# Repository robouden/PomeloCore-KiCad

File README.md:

# Pomelo Core

**Pomelo Core** is a compact radiation detection board featuring a Silicon Photomultiplier (SiPM) based sensor system with integrated high-voltage generation, analog signal processing, and USB connectivity.

## 📋 Features

- **Microcontroller**: ATSAML21G18B (ARM Cortex-M0+, 256KB Flash, 32KB RAM)
- **SiPM Interface**: Complete analog frontend with adjustable HV bias (30-70V)
- **Power Management**: Multi-rail power supply (3.3V, 3.0V, Vload, Vbias)
- **Connectivity**: USB-C interface with ESD protection
- **Debug**: 10-pin J-LINK SWD interface + 18 test points
- **Expansion**: Multiple GPIO headers for external interfaces
- **Compact**: 40mm × 100mm 4-layer PCB

## 🔧 Hardware Specifications

### Main Components

| Component | Part Number | Function |
|-----------|-------------|----------|
| MCU | ATSAML21G18B-AUT | Main microcontroller (48-pin QFN) |
| USB | USB3.1C16PFSMT | USB-C connector (USB 2.0) |
| LDO 3.3V | XC6209F332MR-G | Main 3.3V regulator |
| LDO 3.0V | TPS7A2030PDBVR | 3.0V rail for analog |
| LDO Vload | LT3014BHVES5 | Low-noise LDO for HV control |
| OpAmp | OPA357AIDBVR | Shaper amplifier |
| Comparator | TLV3201AIDBVT | Fast comparator |
| Latch | MC14043BDR2G | Digital latch for triggering |

### SiPM Sensor

- **Part Number**: AFBR-S4N44P014M (Broadcom)
- **Type**: NUV-HD Silicon Photomultiplier
- **Active Area**: 4×4 mm²
- **Spectral Range**: 350-900 nm (peak sensitivity ~420 nm)
- **Datasheet**: [AFBR-S4N44P014M Documentation](https://docs.broadcom.com/doc/AFBR-S4N44P014M-NUV-MT-Silicon-Photomultiplier)

### Scintillator Crystal

- **Material**: CsI(Tl) - Cesium Iodide doped with Thallium
- **Dimensions**: 10 mm × 10 mm × 20 mm
- **Emission Peak**: ~550 nm (matches SiPM sensitivity)
- **Application**: Gamma ray detection coupled to SiPM

### Power Supply

- **Input**: 4.5-6V via USB-C or external connector
- **Output Rails**:
  - 3.3V @ up to 200mA (digital)
  - 3.0V @ up to 100mA (analog)
  - Vload (adjustable)
  - Vbias: 30-70V @ low current (SiPM bias)

### HV Generation

The board features an integrated **boost converter + linear regulator** topology for SiPM bias generation:

- **Boost Stage**: PWM-controlled (L1 10mH inductor, Q3 P-FET, D9 Schottky)
- **Regulation**: LT3014 ultra-low-noise LDO
- **Control**: MCU DAC output (PA02_DAC_HV) sets target voltage
- **Monitoring**: Comparator feedback (PB10_HV_COMP_OUT)
- **Output**: Adjustable 30-70V Vbias for SiPM

## 📁 Project Structure

```
PomeloCore-KiCad/
├── Polemo Core/
│   └── Polemo Core 2/
│       ├── Polemo Core 2.kicad_pro       # KiCad project file
│       ├── Polemo Core 2.kicad_sch       # Schematic (organized in functional blocks)
│       ├── Polemo Core 2.kicad_pcb       # PCB layout (4-layer, 40×100mm)
│       └── Polemo Core 2-backups/        # Automatic backups
├── BOM.csv                                # Bill of Materials
├── v1_2/                                  # Version 1.2 reference files
│   └── schematic/
│       └── PomeloCore.pdf                 # V1.2 schematic PDF
└── README.md                              # This file
```

## 🎨 Schematic Organization

The schematic is organized into **7 functional blocks**:

1. **USB & POWER INPUT**: USB-C interface, power connectors, reset button
2. **POWER MANAGEMENT**: LDOs, inductors, power distribution
3. **MCU CORE**: Microcontroller, crystal, decoupling
4. **ANALOG FRONTEND**: SiPM signal chain, opamps, comparators
5. **LOGIC & CONTROL**: Digital logic, latches, level shifters
6. **EXPANSION I/O**: Pin headers for external connections
7. **DEBUG & TEST**: J-LINK interface, test points

## 🔌 Pinout & Interfaces

### J-LINK Debug Header (10-pin)
```
1: VCC        2: SWDIO
3: GND        4: SWCLK
5: GND        6: SWO
7: NC         8: NC
9: GND       10: RESET
```

### Expansion Headers

- **H2, H3**: 7-pin GPIO expansion
- **H5**: 7-pin expansion with labeled signals
- **MEAS1**: 2-pin measurement header
- **P1, P2**: 2×2 power connectors (mirrored on Pomelo Physics board)

### Key Signals

| Signal | Description |
|--------|-------------|
| SiPM_A | SiPM analog input |
| Vbias | SiPM bias voltage output |
| SHAPER_OUT | Shaped pulse output |
| PA02_DAC_HV | HV control DAC output |
| PA10_PWM | Boost converter PWM |
| PB03_PEAKDET_EN | Peak detector enable |
| PA23_TRG_OUT | Trigger output |

## 📊 Version History

### V1.3 (Current)
**Major improvements over V1.2:**

✅ **Added (47 components)**:
- USB-C connector (USBC1)
- Reset button (BUT1)
- J-LINK debug header
- 18 test points (TP1-TP18)
- Additional transistors (Q4, Q5) and diodes (D6, D8, D10)
- 15 new resistors for better signal conditioning

✅ **Changed**:
- C44: 1uF → 4.7uF
- C45: 4.7uF → 1uF
- H2, H3: 6-pin → 7-pin headers (expanded)

✅ **Enhanced**:
- Better debugging capability
- Improved power filtering
- More flexible I/O expansion

### V1.2 (Legacy)
- Initial production version
- PDF schematic available in `v1_2/schematic/`

## 🚀 Getting Started

### Prerequisites

- **KiCad 9.0** or later
- Basic understanding of radiation detection and SiPM operation
- JTAG/SWD programmer (e.g., J-Link, ST-Link)

### Opening the Project

1. Clone this repository
2. Open `Polemo Core/Polemo Core 2/Polemo Core 2.kicad_pro` in KiCad
3. The schematic shows functional blocks with dashed rectangles
4. The PCB has components organized by function

### Manufacturing

**PCB Specifications:**
- **Layers**: 4 (signal/GND/VCC/signal)
- **Dimensions**: 40mm × 100mm
- **Thickness**: 1.6mm
- **Copper**: 35μm (1oz) on all layers
- **Min Track/Space**: 0.15mm / 0.15mm (for 0805 components)
- **Finish**: HASL or ENIG recommended
- **Solder Mask**: Green (top and bottom)

**Assembly Notes:**
- Minimum component size: 0805 for passives
- QFN-48 MCU requires reflow soldering
- LDOs are SOT-23-5 packages
- Test points for easy debugging

## 📝 Design Notes

### Power Planes
- **Layer 1 (In1.Cu)**: GND plane - solid pour for low noise
- **Layer 2 (In2.Cu)**: VCC plane - split for 3.3V/3.0V rails

### Critical Traces
- Keep SiPM analog traces short and shielded
- HV traces (Vbias) should be isolated from digital signals
- Crystal traces should be short with GND guard ring

### Component Placement
Components are organized into functional blocks:
- Power supply on left side
- MCU in center
- Analog section on right
- Digital logic bottom-right

## 🔬 Applications

- Radiation detection and measurement
- Scintillation counting
- Environmental monitoring
- Educational radiation physics
- DIY Geiger counter replacement with better sensitivity

## 👥 Credits

**Designer**: M. Cuciuc
**Organization**: Safecast
**Date**: 2024-2025

## 📄 License

This hardware design is open source. Please check individual files for specific license terms.

Firmware and software components may have separate licenses.

## 🤝 Contributing

Contributions are welcome! Please:

1. Fork the repository
2. Create a feature branch
3. Make your changes
4. Submit a pull request

For major changes, please open an issue first to discuss what you would like to change.

## 📞 Support

- **Project Page**: [Pomelo on Crowd Supply](https://www.crowdsupply.com/pomelo-instrumentation/pomelo)
- **Safecast**: [https://safecast.org](https://safecast.org)
- Report issues through the repository's issue tracker

## ⚠️ Safety Warning

This board generates **high voltage** (up to 70V) for SiPM biasing. Handle with care:
- Do not touch HV traces while powered
- Use proper ESD protection
- Follow safe electronics handling practices
- Designed for educational and research purposes

---

**Made with ❤️ for the radiation detection community**

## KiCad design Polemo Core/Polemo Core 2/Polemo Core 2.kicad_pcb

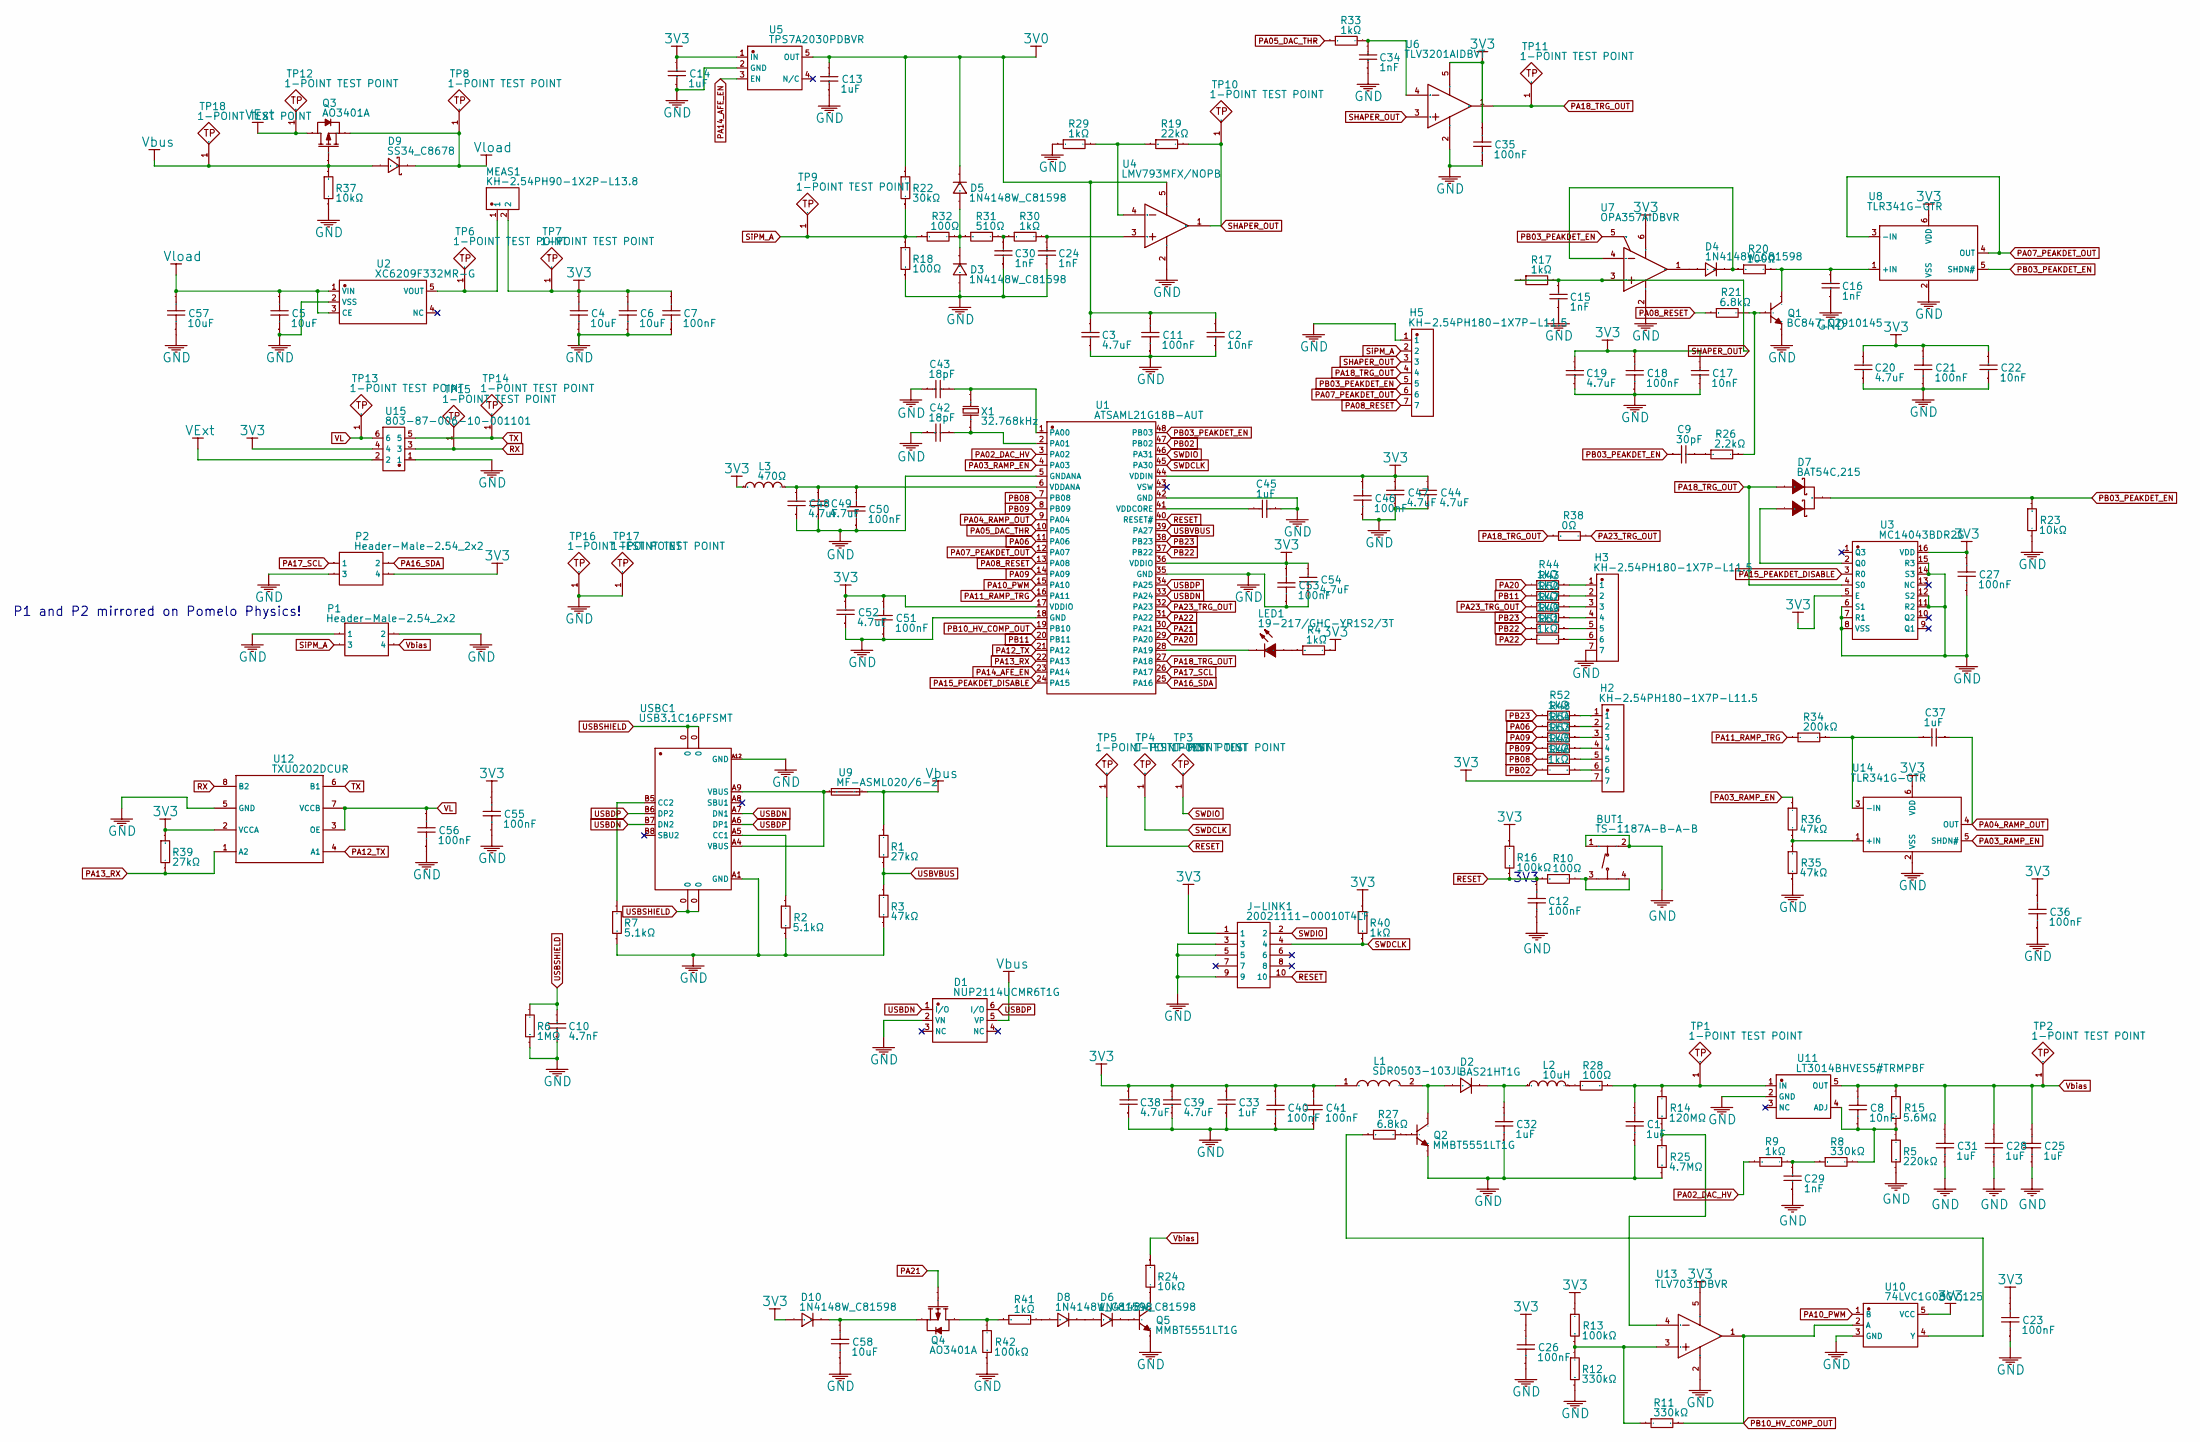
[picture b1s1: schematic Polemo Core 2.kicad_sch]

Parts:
BUT1: TS-1187A-B-A-B; SW_SPST_TL3342; Manufacturer Part TS-1187A-B-A-B
C1, C32: 1uF; C_0805_2012Metric; Manufacturer Part GRM55DR72D105KW01L
C2, C17, C22: 10nF; C_0805_2012Metric; Manufacturer Part 0603B103K500NT
C3, C19, C20: 4.7uF; C_0805_2012Metric; Manufacturer Part 1206B475K500NT
C4, C5, C6, C57, C58: 10uF; C_1206_3216Metric; Manufacturer Part CL10A106KP8NNNC
C7, C11, C12, C18, C21, C23, C26, C27, C35, C36, C40, C41, C46, C50, C51, C53, C55, C56: 100nF; C_0805_2012Metric; Manufacturer Part CC0603KRX7R9BB104
C8: 10nF; C_0805_2012Metric; Manufacturer Part 12062C103KAT2A
C9: 30pF; C_0805_2012Metric; Manufacturer Part 0603CG300J500NT
C10: 4.7nF; C_0805_2012Metric; Manufacturer Part 0603B472K500NT
C13, C14, C33, C37, C45: 1uF; C_0805_2012Metric; Manufacturer Part CL10A105KB8NNNC
C15, C16, C24, C29, C30, C34: 1nF; C_0805_2012Metric; Manufacturer Part CL10B102KB8NNNC
C25, C28, C31: 1uF; C_0805_2012Metric; Manufacturer Part 08051C105KAT2A
C38, C39: 4.7uF; C_1812_4532Metric; Manufacturer Part 1206B475K500NT
C42, C43: 18pF; C_0805_2012Metric; Manufacturer Part CL10C180JB8NNNC
C44, C47, C48, C49, C52, C54: 4.7uF; C_0805_2012Metric; Manufacturer Part CL10A475KO8NNNC
D1: NUP2114UCMR6T1G; SO-8_3.9x4.9mm_P1.27mm; Manufacturer Part NUP2114UCMR6T1G
D2: BAS21HT1G; SOT-23; Manufacturer Part BAS21HT1G
D3, D4, D5, D6, D8, D10: 1N4148W_C81598; D_SOD-123; Manufacturer Part 1N4148W
D7: BAT54C,215; SOT-23; Manufacturer Part BAT54C,215
D9: SS34_C8678; D_SMA; Manufacturer Part SS34
H2, H3, H5: KH-2.54PH180-1X7P-L11.5; PinHeader_1x07_P2.54mm_Vertical; Manufacturer Part KH-2.54PH180-1X7P-L11.5
J-LINK1: 20021111-00010T4LF; PinHeader_2x05_P2.54mm_Vertical; Manufacturer Part 20021111-00010T4LF
L1: SDR0503-103JL; L_0805_2012Metric
L2: 10uH; L_1210_3225Metric; Manufacturer Part SDFL1608S100KTF
L3: 470Ω; L_1210_3225Metric; Manufacturer Part BLM18PG471SN1D
LED1: 19-217/GHC-YR1S2/3T; LED_0805_2012Metric; Manufacturer Part 19-217/GHC-YR1S2/3T
MEAS1: KH-2.54PH90-1X2P-L13.8; PinHeader_1x02_P2.54mm_Vertical; Manufacturer Part KH-2.54PH90-1X2P-L13.8
P1, P2: Header-Male-2.54_2x2; PinHeader_2x02_P2.54mm_Vertical; Manufacturer Part 2.54-2*2P针
Q1: BC847_C2910145; SOT-23; Manufacturer Part BC847
Q2, Q5: MMBT5551LT1G; SOT-23; Manufacturer Part MMBT5551LT1G
Q3, Q4: AO3401A; SOT-23; Manufacturer Part AO3401A
R1, R39: 27kΩ; R_0805_2012Metric; Manufacturer Part 0603WAF2702T5E
R2, R7: 5.1kΩ; R_0805_2012Metric; Manufacturer Part 0603WAF5101T5E
R3, R35, R36: 47kΩ; R_0805_2012Metric; Manufacturer Part 0603WAF4702T5E
R4, R9, R17, R29, R30, R33, R40, R41, R43, R44, R45, R46, R47, R48, R49, R50, R51, R52, R53, R54: 1kΩ; R_0805_2012Metric; Manufacturer Part 0603WAF1001T5E
R5: 220kΩ; R_0805_2012Metric; Manufacturer Part 0603WAF2203T5E
R6: 1MΩ; R_0805_2012Metric; Manufacturer Part 0603WAF1004T5E
R8, R11, R12: 330kΩ; R_0805_2012Metric; Manufacturer Part 0603WAF3303T5E
R10, R18, R20, R28, R32: 100Ω; R_0805_2012Metric; Manufacturer Part 0603WAF1000T5E
R13, R16, R42: 100kΩ; R_0805_2012Metric; Manufacturer Part 0603WAF1003T5E
R14: 120MΩ; R_0805_2012Metric; Manufacturer Part 0603WAF4704T5E
R15: 5.6MΩ; R_0805_2012Metric; Manufacturer Part 0603WAF5604T5E
R19: 22kΩ; R_0805_2012Metric; Manufacturer Part 0603WAF2202T5E
R21, R27: 6.8kΩ; R_0805_2012Metric; Manufacturer Part 0603WAF6801T5E
R22: 30kΩ; R_0805_2012Metric; Manufacturer Part 0603WAF3002T5E
R23, R24, R37: 10kΩ; R_0805_2012Metric; Manufacturer Part 0603WAF1002T5E
R25: 4.7MΩ; R_0805_2012Metric; Manufacturer Part 0603WAF4704T5E
R26: 2.2kΩ; R_0805_2012Metric; Manufacturer Part 0603WAF2201T5E
R31: 510Ω; R_0805_2012Metric; Manufacturer Part 0603WAF5100T5E
R34: 200kΩ; R_0805_2012Metric; Manufacturer Part 0603WAF2003T5E
R38: 0Ω; R_0805_2012Metric; Manufacturer Part 0603WAF0000T5E
TP1, TP2, TP3, TP4, TP5, TP6, TP7, TP8, TP9, TP10, TP11, TP12, TP13, TP14, TP15, TP16, TP17, TP18: 1-POINT TEST POINT; TestPoint_Pad_D1.5mm
U1: ATSAML21G18B-AUT; QFN-48-1EP_7x7mm_P0.5mm_EP5.15x5.15mm; Manufacturer Part ATSAML21G18B-AUT
U2: XC6209F332MR-G; SOT-23-5; Manufacturer Part XC6209F332MR-G
U3: MC14043BDR2G; SOIC-16_3.9x9.9mm_P1.27mm; Manufacturer Part MC14043BDR2G
U4: LMV793MFX/NOPB; MSOP-8_3x3mm_P0.65mm; Manufacturer Part LMV793MFX/NOPB
U5: TPS7A2030PDBVR; SOT-23-5; Manufacturer Part TPS7A2030PDBVR
U6: TLV3201AIDBVT; SOT-23-5; Manufacturer Part TLV3201AIDBVT
U7: OPA357AIDBVR; SOT-23-5; Manufacturer Part OPA357AIDBVR
U8, U14: TLR341G-GTR; SOT-23-6; Manufacturer Part TLR341G-GTR
U9: MF-ASML020/6-2; SOIC-8_3.9x4.9mm_P1.27mm; Manufacturer Part MF-ASML020/6-2
U10: 74LVC1G08GV,125; SOT-353_SC-70-5; Manufacturer Part 74LVC1G08GV,125
U11: LT3014BHVES5#TRMPBF; SOT-23-5; Manufacturer Part LT3014BHVES5#TRMPBF
U12: TXU0202DCUR; VSSOP-8_2.3x2mm_P0.5mm; Manufacturer Part TXB0102DCUR
U13: TLV7031DBVR; SOT-23-5; Manufacturer Part TLV7031DBVR
U15: 803-87-006-10-001101; PinSocket_1x06_P2.54mm_Vertical; Manufacturer Part 803-87-006-10-001101
USBC1: USB3.1C16PFSMT; USB_C_Receptacle_HRO_TYPE-C-31-M-12
X1: 32.768kHz; Crystal_SMD_3225-4Pin_3.2x2.5mm; Manufacturer Part Q13FC1350000400

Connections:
3V0: C2.2, C3.2, C11.2, C13.2, D5.1 (K), R22.2, U4.5 (V+), U5.5 (OUT)
3V3: C4.2, C6.2, C7.2, C14.2, C17.2, C18.2, C19.2, C20.2, C21.2, C22.2, C23.2, C26.2, C27.2, C33.2, C35.2, C36.2, C38.2, C39.2, C40.2, C41.2, C44.2, C46.2, C47.2, C51.2, C52.2, C53.2, C54.2, C55.2, D10.2 (A), H2.7, J-LINK1.1, L1.1, L3.1, MEAS1.2, P2.4, R4.2, R13.2, R16.2, R39.1, R40.2, TP7.1, U1.17 (VDDIO), U1.36 (VDDIO), U1.44 (VDDIN), U3.5 (E), U3.16 (VDD), U5.1 (IN), U6.5 (VCC), U7.6 (V+), U8.6 (VDD), U10.5 (VCC), U12.2 (VCCA), U13.5 (VCC), U14.6 (VDD), U15.4
GND: BUT1.1 (A), BUT1.2 (B), C1.1, C2.1, C3.1, C4.1, C5.1, C6.1, C7.1, C10.1, C11.1, C12.2, C13.1, C14.1, C15.1, C16.1, C17.1, C18.1, C19.1, C20.1, C21.1, C22.1, C23.1, C24.1, C25.1, C26.1, C27.1, C28.1, C29.1, C30.1, C31.1, C32.1, C33.1, C34.1, C35.1, C36.1, C38.1, C39.1, C40.1, C41.1, C42.1, C43.1, C44.1, C45.1, C46.1, C47.1, C48.1, C49.1, C50.1, C51.1, C52.1, C53.1, C54.1, C55.1, C56.1, C57.1, C58.1, D1.2 (VN), D3.2 (A), H3.7, H5.1, J-LINK1.3, J-LINK1.5, J-LINK1.9, P1.1, P1.2, P2.3, Q1.2 (E), Q2.2 (E), Q5.2 (E), R2.1, R3.1, R5.1, R6.1, R7.1, R12.1, R18.1, R23.2, R25.1, R29.1, R35.1, R37.2, R42.1, TP16.1, TP17.1, U1.5 (GNDANA), U1.18 (GND), U1.35 (GND), U1.42 (GND), U2.2 (VSS), U3.6 (S1), U3.7 (R1), U3.8 (VSS), U3.11 (R2), U3.12 (S2), U3.14 (S3), U3.15 (R3), U4.2 (V-), U5.2 (GND), U6.2 (GND), U7.2 (V-), U8.2 (VSS), U10.3 (GND), U11.2 (GND), U12.5 (GND), U13.2 (VEE), U14.2 (VSS), U15.1, USBC1.A1 (GND), USBC1.A12 (GND)
unnamed: BUT1.3 (C), BUT1.4 (D), R10.2
unnamed: C9.2, R26.1
unnamed: C29.2, R8.1, R9.2
unnamed: C30.2, R30.1, R31.2
unnamed: D2.2 (A), L1.2, Q2.3 (C)
unnamed: C32.2, D2.1 (C), L2.1
unnamed: D3.1 (K), D5.2 (A), R31.1, R32.2
unnamed: D4.2 (A), U7.1 (OUT)
unnamed: D4.1 (K), R20.1, U7.4 (IN-)
unnamed: D6.2 (A), D8.1 (K)
unnamed: D6.1 (K), Q5.1 (B)
unnamed: D8.2 (A), R41.2
unnamed: C58.2, D10.1 (K), Q4.2 (S)
unnamed: H2.1, R52.1
unnamed: H2.2, R48.1
unnamed: H2.3, R54.1
unnamed: H2.4, R53.1
unnamed: H2.5, R45.1
unnamed: H2.6, R46.1
unnamed: H3.1, R44.1
unnamed: H3.2, R43.1
unnamed: H3.3, R50.1
unnamed: H3.4, R47.1
unnamed: H3.5, R49.1
unnamed: H3.6, R51.1
unnamed: L2.2, R28.2
unnamed: LED1.2 (A), R4.1
unnamed: LED1.1 (C), U1.28 (PA19)
unnamed: Q1.1 (B), R21.2, R26.2
unnamed: C16.2, Q1.3 (C), R20.2, U8.1 (+IN)
unnamed: Q2.1 (B), R27.2
unnamed: Q4.3 (D), R41.1, R42.2
unnamed: Q5.3 (C), R24.2
unnamed: C43.2, U1.1 (PA00), X1.2
unnamed: C42.2, U1.2 (PA01), X1.1
unnamed: C48.2, C49.2, C50.2, L3.2, U1.6 (VDDANA)
unnamed: C45.2, U1.41 (VDDCORE)
unnamed: MEAS1.1, TP6.1, U2.5 (VOUT)
unnamed: D7.2 (A), U3.2 (Q0)
unnamed: C24.2, R30.2, U4.3 (+IN)
unnamed: R19.1, R29.2, U4.4 (-IN)
unnamed: C34.2, R33.2, U6.4 (VIN-)
unnamed: U9.1, USBC1.A4 (VBUS), USBC1.A9 (VBUS)
unnamed: R27.1, U10.4 (Y)
unnamed: C8.1, R5.2, R8.2, R15.1, U11.4 (ADJ)
unnamed: C1.2, R14.2, R28.1, TP1.1, U11.1 (IN)
unnamed: R11.2, R12.2, R13.1, U13.3 (IN+)
unnamed: R14.1, R25.2, U13.4 (IN-)
unnamed: R35.2, R36.1, U14.1 (+IN)
unnamed: C37.2, R34.2, U14.3 (-IN)
unnamed: R2.2, USBC1.A5 (CC1)
unnamed: R7.2, USBC1.B5 (CC2)
PA02_DAC_HV: R9.1, U1.3 (PA02)
PA03_RAMP_EN: R36.2, U1.4 (PA03), U14.5 (SHDN#)
PA04_RAMP_OUT: C37.1, U1.9 (PA04), U14.4 (OUT)
PA05_DAC_THR: R33.1, U1.10 (PA05)
PA06: R48.2, U1.11 (PA06)
PA07_PEAKDET_OUT: H5.6, U1.12 (PA07), U8.3 (-IN), U8.4 (OUT)
PA08_RESET: H5.7, R21.1, U1.13 (PA08)
PA09: R54.2, U1.14 (PA09)
PA10_PWM: U1.15 (PA10), U10.1 (B)
PA11_RAMP_TRG: R34.1, U1.16 (PA11)
PA12_TX: U1.21 (PA12), U12.4 (A1)
PA13_RX: R39.2, U1.22 (PA13), U12.1 (A2)
PA14_AFE_EN: U1.23 (PA14), U5.3 (EN)
PA15_PEAKDET_DISABLE: U1.24 (PA15), U3.3 (R0)
PA16_SDA: P2.2, U1.25 (PA16)
PA17_SCL: P2.1, U1.26 (PA17)
PA18_TRG_OUT: D7.1 (A), H5.4, R38.1, TP11.1, U1.27 (PA18), U3.4 (S0), U6.1 (OUT)
PA20: R44.2, U1.29 (PA20)
PA21: Q4.1 (G), U1.30 (PA21)
PA22: R51.2, U1.31 (PA22)
PA23_TRG_OUT: R38.2, R50.2, U1.32 (PA23)
PB02: R46.2, U1.47 (PB02)
PB03_PEAKDET_EN: C9.1, D7.3 (K), H5.5, R23.1, U1.48 (PB03), U7.5 (ENABLE), U8.5 (SHDN#)
PB08: R45.2, U1.7 (PB08)
PB09: R53.2, U1.8 (PB09)
PB10_HV_COMP_OUT: R11.1, U1.19 (PB10), U10.2 (A), U13.1 (OUT)
PB11: R43.2, U1.20 (PB11)
PB22: R49.2, U1.37 (PB22)
PB23: R47.2, R52.2, U1.38 (PB23)
RESET: C12.1, J-LINK1.10, R10.1, R16.1, TP5.1, U1.40 (RESET#)
RX: TP15.1, U12.8 (B2), U15.3
SHAPER_OUT: C15.2, H5.3, R17.1, R17.2, R19.2, TP10.1, U4.1 (OUTPUT), U6.3 (VIN+), U7.3 (IN+)
SWDCLK: J-LINK1.4, R40.1, TP4.1, U1.45 (PA30)
SWDIO: J-LINK1.2, TP3.1, U1.46 (PA31)
SiPM_A: H5.2, P1.3, R18.2, R22.1, R32.1, TP9.1
TX: TP14.1, U12.6 (B1), U15.5
USBDN: D1.1 (I/O), U1.33 (PA24), USBC1.A7 (DN1), USBC1.B7 (DN2)
USBDP: D1.6 (I/O), U1.34 (PA25), USBC1.A6 (DP1), USBC1.B6 (DP2)
USBSHIELD: C10.2, R6.2, USBC1.0
USBVBUS: R1.1, R3.2, U1.39 (PA27)
VExt: Q3.3 (D), TP12.1, U15.2
VL: C56.2, TP13.1, U12.3 (OE), U12.7 (VCCB), U15.6
Vbias: C8.2, C25.2, C28.2, C31.2, P1.4, R15.2, R24.1, TP2.1, U11.5 (OUT)
Vbus: D1.5 (VP), D9.2 (A), Q3.1 (G), R1.2, R37.1, TP18.1, U9.2
Vload: C5.2, C57.2, D9.1 (K), Q3.2 (S), TP8.1, U2.1 (VIN), U2.3 (CE)

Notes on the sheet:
3V3
P1 and P2 mirrored on Pomelo Physics!

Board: 4 copper layers, 174 parts (0 on the bottom side), 99 nets, no tracks yet.

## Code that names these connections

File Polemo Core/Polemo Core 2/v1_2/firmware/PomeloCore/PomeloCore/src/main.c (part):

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static void isr_vbus_callback(void)
{
	volatile uint8_t a;
	a = port_pin_get_input_level(PIN_PA09);
	isr_vbus = true;
}

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	static uint16_t adc_val, rnd, i;
	static volatile bool pinValue;
	static uint32_t l_gammaTime;
	pinValue = port_pin_get_input_level(PIN_PB02);

	if (daq_enabled)
	{
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		while (adc_read(&adc_instance_app, &adc_val) == STATUS_BUSY) ;

		// Clear peak detector capacitor
		port_pin_set_output_level(PIN_PA08, 1);
		port_pin_set_output_level(PIN_PA15, 1);
		nop(); nop(); nop(); nop(); nop(); // 5us. Aaaactually almost nothing
		port_pin_set_output_level(PIN_PA15, 0);
		port_pin_set_output_level(PIN_PA08, 0);


		if (gammaDaqRun)
		{
			port_pin_set_output_level(PIN_PA19, 0);
			
			adc_val >>= 2;
			
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
			if (gammaCoincidence)
			{
				if (port_pin_get_input_level(PIN_PA20))
				{
					gammaSpectrumCoincidence[adc_val]++;
					gammaPulseCoincidenceN++;
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					}
					
					// Assert our ACK line
					port_pin_set_output_level(PIN_PB11, 1);
					// Loop while monitor line is still high
					while (port_pin_get_input_level(PIN_PA20)) ;
					// Deassert our ACK line
					port_pin_set_output_level(PIN_PB11, 0);
				}
			}
			else
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			
		}

		port_pin_set_output_level(PIN_PA19, 1);
		
		// Try to fix subthreshold structures. Retriggering of this interrupt can
		// cause a 2nd reading, after the peak detector had already been cleared
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	struct ccl_lut_config ccl_lut_conf;
	struct system_pinmux_config pinmux_config;

	// Set PA22 as remote trigger input - CCL2 In0
	system_pinmux_get_config_defaults(&pinmux_config);
	pinmux_config.mux_position = 8;
	pinmux_config.direction    = SYSTEM_PINMUX_PIN_DIR_INPUT;
	pinmux_config.input_pull   = SYSTEM_PINMUX_PIN_PULL_DOWN;
	system_pinmux_pin_set_config(PIN_PA22, &pinmux_config);

	// Set PA23 as local trigger input - CCL2 In1
	system_pinmux_get_config_defaults(&pinmux_config);
	pinmux_config.mux_position = 8;
	pinmux_config.direction    = SYSTEM_PINMUX_PIN_DIR_INPUT;
	pinmux_config.input_pull   = SYSTEM_PINMUX_PIN_PULL_DOWN;
	system_pinmux_pin_set_config(PIN_PA23, &pinmux_config);

	// Set PB22 as ACK0 input - CCL0 In0
	system_pinmux_get_config_defaults(&pinmux_config);
	pinmux_config.mux_position = 8;
	pinmux_config.direction    = SYSTEM_PINMUX_PIN_DIR_INPUT;
	pinmux_config.input_pull   = SYSTEM_PINMUX_PIN_PULL_DOWN;
	system_pinmux_pin_set_config(PIN_PB22, &pinmux_config);

	// Set PA06 as ACK1 input - CCL0 In2
	system_pinmux_get_config_defaults(&pinmux_config);
	pinmux_config.mux_position = 8;
	pinmux_config.direction    = SYSTEM_PINMUX_PIN_DIR_INPUT;
	pinmux_config.input_pull   = SYSTEM_PINMUX_PIN_PULL_DOWN;
	system_pinmux_pin_set_config(PIN_PA06, &pinmux_config);

	// Set PB23 as coincidences output - CCL0 out
	system_pinmux_get_config_defaults(&pinmux_config);
	pinmux_config.mux_position = 8;
	pinmux_config.direction    = SYSTEM_PINMUX_PIN_DIR_OUTPUT_WITH_READBACK;
	system_pinmux_pin_set_config(PIN_PB23, &pinmux_config);

	ccl_module_reset();

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	system_pinmux_get_config_defaults(&pinmux_config);
	pinmux_config.mux_position = 7;
	pinmux_config.direction    = PORT_PIN_DIR_OUTPUT;
	system_pinmux_pin_set_config(PIN_PA10, &pinmux_config);
}

void hv_disable(void)
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
	// HV PWM output 0
	pin_conf.direction  = PORT_PIN_DIR_OUTPUT;
	port_pin_set_config(PIN_PA10, &pin_conf);
	port_pin_set_output_level(PIN_PA10, 0);
	
	// Pulse HV crowbar
	port_pin_set_output_level(PIN_PA21, 0);
	delay_ms(10);
	port_pin_set_output_level(PIN_PA21, 1);
}

void hv_boost(bool boostOn)
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	pinmux_config.direction    = SYSTEM_PINMUX_PIN_DIR_INPUT;
	pinmux_config.input_pull   = SYSTEM_PINMUX_PIN_PULL_NONE;
	pinmux_config.powersave    = false;
	system_pinmux_pin_set_config(PIN_PA18, &pinmux_config);

	spi_transceive_wait(&spi_instance_app, 0xFF, &rx_data);
	spi_transceive_wait(&spi_instance_app, 0xFF, &rx_data);
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	uint16_t rx_data_1;
	
	// One-shot conversion request
	port_pin_set_output_level(PIN_PA27, 0);
	spi_transceive_wait(&spi_instance_app, 0x00, &rx_data_0);
	spi_transceive_wait(&spi_instance_app, 0x06, &rx_data_0);
	spi_transceive_wait(&spi_instance_app, 0x16, &rx_data_0);	// One shot mode, 1 Hz conversion rate
	spi_transceive_wait(&spi_instance_app, 0x00, &rx_data_1);
	port_pin_set_output_level(PIN_PA27, 1);

	delay_ms(15);

	// Read result
	port_pin_set_output_level(PIN_PA27, 0);
	spi_transceive_wait(&spi_instance_app, 0x01, &rx_data_0);
	spi_transceive_wait(&spi_instance_app, 0x00, &rx_data_0);
	spi_transceive_wait(&spi_instance_app, 0x00, &rx_data_0);
	spi_transceive_wait(&spi_instance_app, 0x00, &rx_data_0);
	spi_transceive_wait(&spi_instance_app, 0x00, &rx_data_1);
	port_pin_set_output_level(PIN_PA27, 1);

	rx_data_0 |= rx_data_1 << 8;
	rx_data_0 >>= 2;
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	
	// Ramp generator enable
	pin_conf.direction  = PORT_PIN_DIR_OUTPUT;
	port_pin_set_config(PIN_PA03, &pin_conf);
	port_pin_set_output_level(PIN_PA03, 1);

	// Ramp generator trigger
	pin_conf.direction  = PORT_PIN_DIR_OUTPUT;
	port_pin_set_config(PIN_PA11, &pin_conf);
	port_pin_set_output_level(PIN_PA11, 1);

	adc_val = 4095;
	while (adc_val > 100)
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	
	for (i = 0; i < 1000; i++)
	{
		port_pin_set_output_level(PIN_PA11, 0);
		while (adc_val < 4000)
		{
			adc_start_conversion(&adc_instance_app);
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			gammaSpectrum[adc_val >> 2]++;
		}

		port_pin_set_output_level(PIN_PA11, 1);

		while (adc_val > 100)
		{
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		if (i % 10 == 0) pomelo_sprintf(iFace, "{\"type\":\"calib_progress\", \"payload\":%d}\n", i/10);
	}

	port_pin_set_output_level(PIN_PA11, 0);
	port_pin_set_output_level(PIN_PA03, 0);

	adc_set_positive_input(&adc_instance_app, ADC_POSITIVE_INPUT_PIN7);

	// Ramp generator input
	pin_conf.direction  = PORT_PIN_DIR_INPUT;
	port_pin_set_config(PIN_PA04, &pin_conf);

	pomelo_printf(iFace, "{\"type\":\"calib_spectrum\", \"payload\":{\"data\":[");
	for (i = 0; i < SPECTRUM_LEN - 1; i++)
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	// All pins output low
	pin_conf.direction  = PORT_PIN_DIR_OUTPUT;

	port_pin_set_config(PIN_PA30, &pin_conf);
	port_pin_set_output_level(PIN_PA30, 1);

	port_pin_set_config(PIN_PA31, &pin_conf);
	port_pin_set_output_level(PIN_PA31, 1);

	// USB pins input
	pin_conf.direction  = PORT_PIN_DIR_INPUT;
	pin_conf.input_pull = PORT_PIN_PULL_DOWN;
	port_pin_set_config(PIN_PA24, &pin_conf);
	port_pin_set_config(PIN_PA25, &pin_conf);
}


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		dac_chan_disable(&dac_instance_app, DAC_CHANNEL_0);
		dac_chan_disable(&dac_instance_app, DAC_CHANNEL_1);
		dac_reset(&dac_instance_app);
		port_pin_set_config(PIN_PA02, &pin_conf);
		port_pin_set_output_level(PIN_PA14, 0);

		port_pin_set_output_level(PIN_PA15, 1);
		nop(); nop(); nop(); nop(); nop(); // 5us. Aaaactually almost nothing
		port_pin_set_output_level(PIN_PA15, 0);
	}
}

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		dac_chan_write(&dac_instance_app, DAC_CHANNEL_0, 4095);	// Immediately set a value that drives HV as low as possible
		dac_chan_write(&dac_instance_app, DAC_CHANNEL_1, pomeloParams.threshold);
		update_hv_temp();
		port_pin_set_output_level(PIN_PA14, 1);
		hv_enable();
		daq_enabled = true;
		pomeloParams.sys_power = daq_enabled;
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	
	// LED
	pin_conf.direction  = PORT_PIN_DIR_OUTPUT;
	port_pin_set_config(PIN_PA19, &pin_conf);
	port_pin_set_output_level(PIN_PA19, 1);

	// Reset cap
	pin_conf.direction  = PORT_PIN_DIR_OUTPUT;
	port_pin_set_config(PIN_PA08, &pin_conf);
	port_pin_set_output_level(PIN_PA08, 0);

	// USBVBUS
	pin_conf.direction  = PORT_PIN_DIR_INPUT;
	pin_conf.input_pull = PORT_PIN_PULL_NONE;
	port_pin_set_config(PIN_PA09, &pin_conf);

	// AFE_EN
	pin_conf.direction  = PORT_PIN_DIR_OUTPUT;
	port_pin_set_config(PIN_PA14, &pin_conf);
	port_pin_set_output_level(PIN_PA14, 1);

	// PeakDet disable
	pin_conf.direction  = PORT_PIN_DIR_OUTPUT;
	port_pin_set_config(PIN_PA15, &pin_conf);
	port_pin_set_output_level(PIN_PA15, 0);

	// nCS_TEMP
	pin_conf.direction  = PORT_PIN_DIR_OUTPUT;
	port_pin_set_config(PIN_PA27, &pin_conf);
	port_pin_set_output_level(PIN_PA27, 1);

	// Ramp generator enable
	pin_conf.direction  = PORT_PIN_DIR_OUTPUT;
	port_pin_set_config(PIN_PA03, &pin_conf);
	port_pin_set_output_level(PIN_PA03, 0);

	// Ramp generator trigger
	pin_conf.direction  = PORT_PIN_DIR_OUTPUT;
	port_pin_set_config(PIN_PA11, &pin_conf);
	port_pin_set_output_level(PIN_PA11, 0);

	// Ramp generator input
	pin_conf.direction  = PORT_PIN_DIR_INPUT;
	port_pin_set_config(PIN_PA04, &pin_conf);

	// Trigger input
	pin_conf.direction  = PORT_PIN_DIR_INPUT;
	port_pin_set_config(PIN_PB02, &pin_conf);

	// PeakDet EN input (2nd trigger)
	pin_conf.direction  = PORT_PIN_DIR_INPUT;
	port_pin_set_config(PIN_PB03, &pin_conf);


	// Coincidences monitor line
	pin_conf.direction  = PORT_PIN_DIR_INPUT;
	pin_conf.input_pull = PORT_PIN_PULL_DOWN;
	port_pin_set_config(PIN_PA20, &pin_conf);

	// Coincidences ACK output
	pin_conf.direction  = PORT_PIN_DIR_OUTPUT;
	port_pin_set_config(PIN_PB11, &pin_conf);
	port_pin_set_output_level(PIN_PB11, 0);


	// Coincidences synchronizer output
	pin_conf.direction  = PORT_PIN_DIR_OUTPUT;
	port_pin_set_config(PIN_PB09, &pin_conf);
	port_pin_set_output_level(PIN_PB09, 0);
	
	// Coincidences synchronizer input
	pin_conf.direction  = PORT_PIN_DIR_INPUT;
	pin_conf.input_pull = PORT_PIN_PULL_DOWN;
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
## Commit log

2025-11-18 Create Initial PomeloCore schematic
2025-11-18 Added PDF of schematic
2025-11-22 Add scripts for assigning footprints to PomeloCore schematic components
    - Implemented assign_footprints_correct.py for initial footprint assignment.
    - Developed assign_footprints_final.py to assign footprints to actual component instances.
    - Created assign_footprints_v2.py to handle KiCad 9 format with symbol instances.
    - Introduced assign_footprints_v3.py to overwrite existing footprints correctly.
    - Added assign_fp_working.py for a streamlined footprint assignment process.
    - Enhanced footprint mapping for various components including resistors, capacitors, diodes, and inductors.
2025-11-23 Added workspace
2025-11-23 Added V1.2 files
2025-11-23 Moved more components around
2025-11-25 Added source code for the firmw.are
2025-11-25 feat: Implement initial project setup for PomeloCore firmware, integrating ASF core, SAM L21 drivers, and project configuration files.
2025-11-29 Added README.md and update many files
2025-11-29 moved many files

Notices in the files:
README.md:
License: MIT
